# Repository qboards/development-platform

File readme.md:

# Modular Development Board

This board is essentially a breakout board for power, communication
and IO ports to a microcontroller or other suitable device. Multiple 
minimal microcontroller boards can be connected and easily swapped out
to have a full featured development board, that is not permanently tied
to a single microcontroller.

> TODO: list of modules

## Dev board Connector

> TODO

### Pinout

| Pin number | Function   |   | Pin number | Function  |   | Pin number | Function |   | Pin number | Function |
|------------|------------|---|------------|-----------|---|------------|----------|---|------------|----------|
|          1 | GND        |   |         21 | PORTA_6   |   |         41 | PORTB_8  |   |         61 | PORTD_2  |
|          2 | GND        |   |         22 | COMM_TX_2 |   |         42 | ICSP4    |   |         62 | PORTE_8  |
|          3 | VBUS       |   |         23 | PORTA_7   |   |         43 | PORTC_1  |   |         63 | PORTD_3  |
|          4 | VBUS       |   |         24 | COMM_RX_2 |   |         44 | ICSP5    |   |         64 | PORTE_7  |
|          5 | 5v         |   |         25 | PORTA_8   |   |         45 | PORTC_2  |   |         65 | PORTD_4  |
|          6 | 5v         |   |         26 | COMM_TX_3 |   |         46 | ICSP6    |   |         66 | PORTE_6  |
|          7 | 3v3        |   |         27 | PORTB_1   |   |         47 | PORTC_3  |   |         67 | PORTD_5  |
|          8 | 3v3        |   |         28 | COMM_RX_3 |   |         48 | ICSP7    |   |         68 | PORTE_5  |
|          9 | 1v8        |   |         29 | PORTB_2   |   |         49 | PORTC_4  |   |         69 | PORTD_6  |
|         10 | 1v8        |   |         30 | COMM_TX_4 |   |         50 | ICSP8    |   |         70 | PORTE_4  |
|         11 | PORTA_1    |   |         31 | PORTB_3   |   |         51 | PORTC_5  |   |         71 | PORTD_7  |
|         12 | COMM_RTS_1 |   |         32 | COMM_RX_4 |   |         52 | ICSP9    |   |         72 | PORTE_3  |
|         13 | PORTA_2    |   |         33 | PORTB_4   |   |         53 | PORTC_6  |   |         73 | PORTD_8  |
|         14 | COMM_CTS_1 |   |         34 | NC        |   |         54 | ICSP10   |   |         74 | PORTE_2  |
|         15 | PORTA_3    |   |         35 | PORTB_5   |   |         55 | PORTC_7  |   |         75 | NC       |
|         16 | COMM_DTR_1 |   |         36 | ICSP1     |   |         56 | NC       |   |         76 | PORTE_1  |
|         17 | PORTA_4    |   |         37 | PORTB_6   |   |         57 | PORTC_8  |   |         77 | VBUS     |
|         18 | COMM_TX_1  |   |         38 | ICSP2     |   |         58 | RST_A    |   |         78 | VBUS     |
|         19 | PORTA_5    |   |         39 | PORTB_7   |   |         59 | PORTD_1  |   |         79 | GND      |
|         20 | COMM_RX_1  |   |         40 | ICSP3     |   |         60 | RST_B    |   |         80 | GND      |

## Power supply

Input power can be delivered through the external power (barrel jack or 
screw terminals) or the USB connector. Selecting power from either the 
external inputs or the USB connector can be done with the **Power source** 
jumper.

Input on the external power terminals should be in the range
of 6 up to 15 volt. The polarity on the external input does not matter,
the development board will correct the polarity.

> TODO: Add current requirements.

The input power is regulated to 5V, 3.3V and 1.8V rails, which are 
all supplied to the development module. The module itself can pick one
of those rails and feed that rail back as VCC. For all rails and the 
ground rail test points are supplied.

> TODO: Add description of protection

## Communication

There are four serial ports that modules can expose, one fully featured (TX, RX, 
DTR, CTS, RTS) and three basic (TX, RX only). The development board has a single
USB to serial UART interface (FTDI FT232RL) connected to the USB input and the
other end can be connected with the jumper interfaces to any of the four serial
connections to the development module.

> TODO: Add image of communication jumpers

There are two LED indicators for TX and RX activity.

## Port modules

> TODO

## In Circuit Programming (ICP)

| ICP Pin | AVR Function |
|---------|--------------|
|       1 | MOSI         |
|       2 | VCC (VBUS)   |
|       3 | Unused (NC)  |
|       4 | GND          |
|       5 | RESET        |
|       6 | GND          |
|       7 | SCK          |
|       8 | GND          |
|       9 | MISO         |
|      10 | GND          |

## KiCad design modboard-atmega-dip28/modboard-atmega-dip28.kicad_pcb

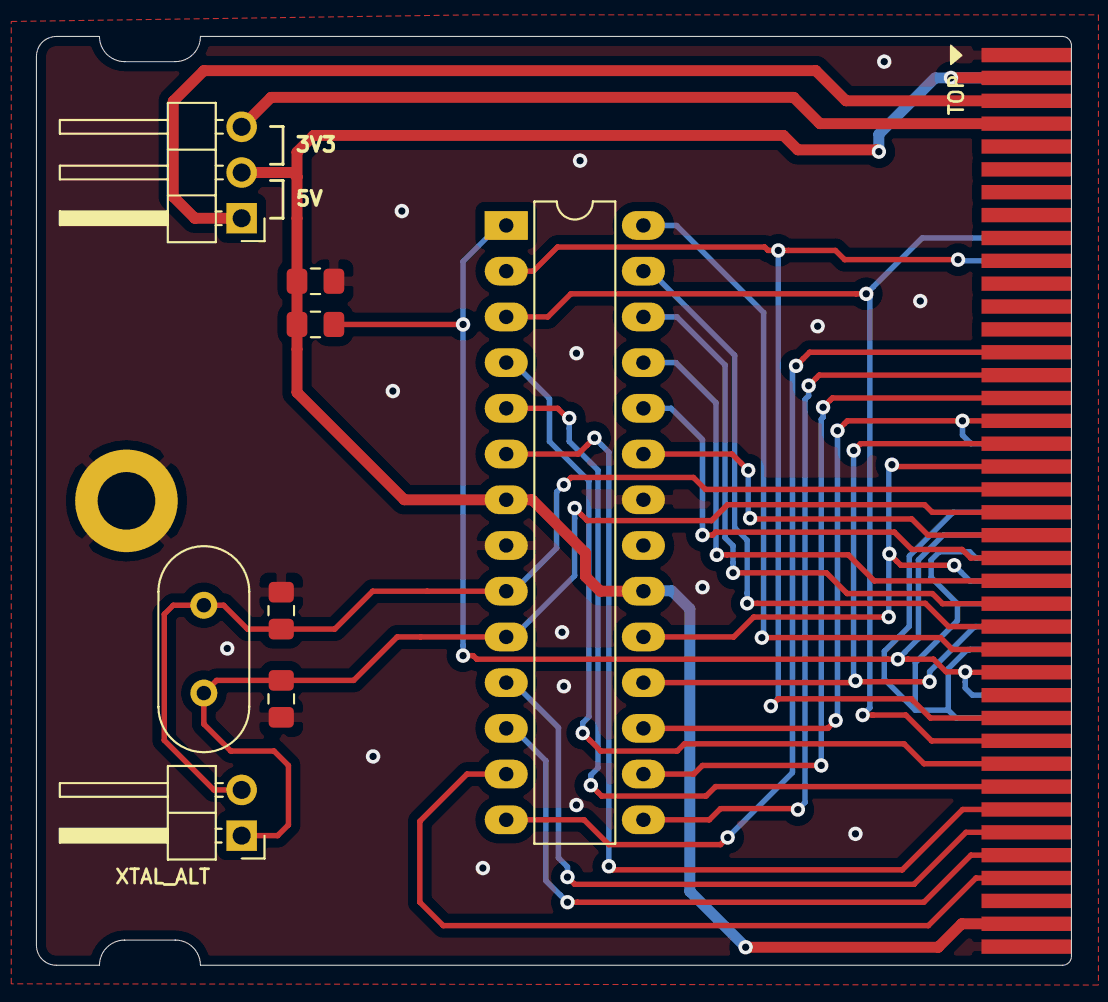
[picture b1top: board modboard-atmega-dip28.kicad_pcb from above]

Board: 2 copper layers, 57.5 x 51.6 mm, 11 parts (1 on the bottom side), 27 nets.

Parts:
ATmega-DIP28: LOGO_BRD_REF; logo_url-5mm
C1, C2, C3: C; C_0805_2012Metric_Pad1.15x1.40mm_HandSolder
H1: MountingHole_Pad; MountingHole_3.2mm_M3_ISO7380_Pad
J1: modboard-edge-connector; modboard_edge_connector
J2: Conn_01x03_Male; PinHeader_1x03_P2.54mm_Horizontal
R1: 10K; R_0805_2012Metric_Pad1.15x1.40mm_HandSolder
U1: ATMEGA328P-PU; DIP-28_W7.62mm_LongPads
XTAL_ALT: Conn_01x02_Male; PinHeader_1x02_P2.54mm_Horizontal
Y1: Crystal; Crystal_HC49-4H_Vertical

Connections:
GND: C1.2, C2.2, C3.2, H1.1, J1.1, J1.2, J1.42, J1.46, J1.50, J1.54, J1.60, J1.79, J1.80, U1.8, U1.22
MISO: J1.35, J1.52, U1.18
MOSI: J1.33, J1.36, U1.17
unnamed: C2.1, J1.39, U1.9, XTAL_ALT.2, Y1.1
unnamed: C3.1, J1.41, U1.10, XTAL_ALT.1, Y1.2
unnamed: J1.5, J1.6, J2.1
unnamed: J1.7, J1.8, J2.3
unnamed: J1.27, U1.14
unnamed: J1.29, U1.15
unnamed: J1.31, U1.16
unnamed: J1.43, U1.23
unnamed: J1.45, U1.24
unnamed: J1.47, U1.25
unnamed: J1.49, U1.26
unnamed: J1.51, U1.27
unnamed: J1.53, U1.28
unnamed: J1.63, U1.4
unnamed: J1.65, U1.5
unnamed: J1.67, U1.6
unnamed: J1.69, U1.11
unnamed: J1.71, U1.12
unnamed: J1.73, U1.13
RESET: J1.44, J1.55, J1.58, R1.2, U1.1
RX: J1.20, J1.59, U1.2
SCK: J1.37, J1.48, U1.19
TX: J1.18, J1.61, U1.3
VCC: C1.1, J1.3, J1.4, J1.77, J1.78, J2.2, R1.1, U1.7, U1.20

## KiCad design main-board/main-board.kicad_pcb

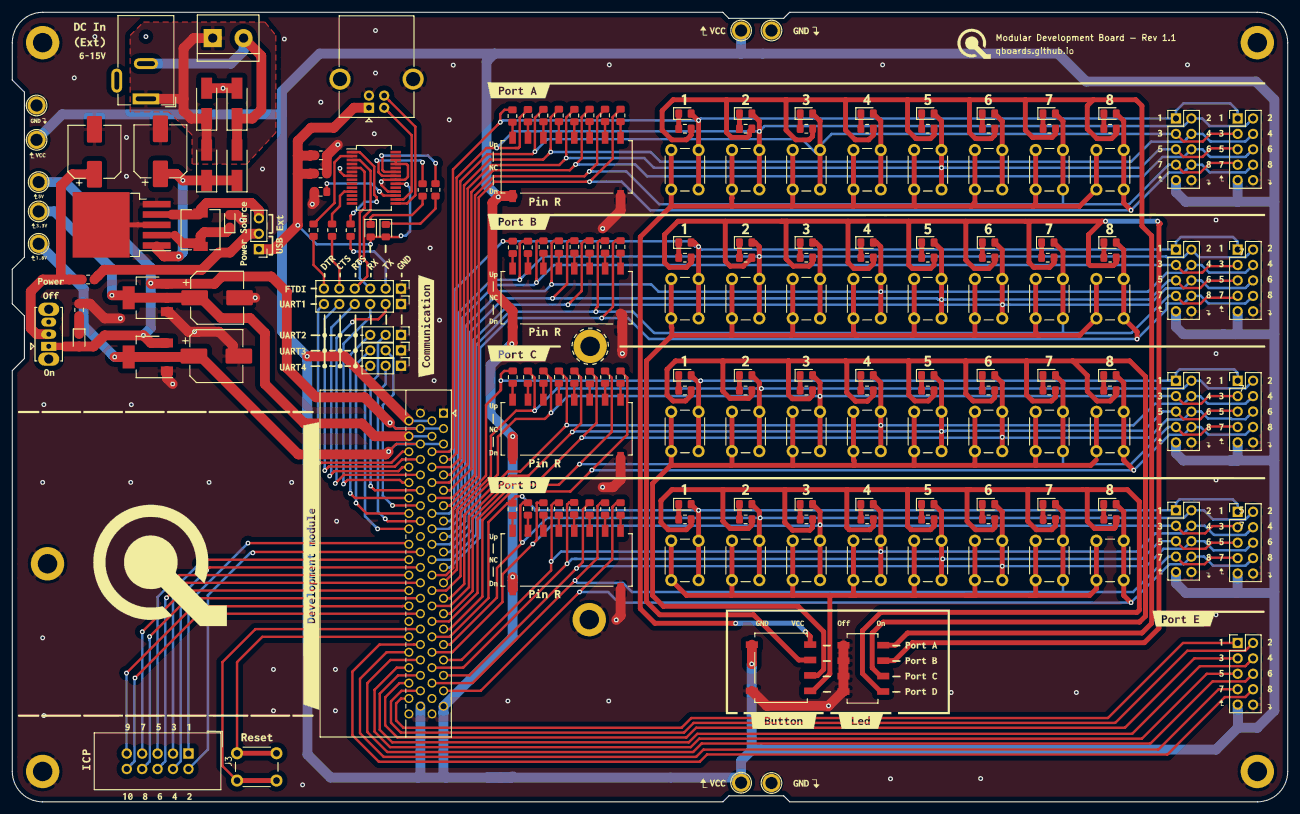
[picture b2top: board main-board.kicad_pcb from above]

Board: 2 copper layers, 210.0 x 130.0 mm, 201 parts (0 on the bottom side), 164 nets.

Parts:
C1: 100uF; CP_Elec_8x10.5
C2: 1000uF; CP_Elec_8x10.5
C3, C4: 22uF; CP_Elec_8x10.5
C5: 10uF; C_0805_2012Metric_Pad1.15x1.40mm_HandSolder
C6, C7: 100nF; C_0805_2012Metric_Pad1.15x1.40mm_HandSolder
D1, D2, D3, D4: 1N4007; D_SMA_Handsoldering
D5: D_Schottky_Small; D_SOD-323_HandSoldering
D6, D7, D8, D9, D10, D11, D12, D13, D14, D15, D16, D17, D18, D19, D20, D21, D22, D23, D24, D25, D26, D27, D28, D29, D30, D31, D32, D33, D34, D35, D36, D37: LED_Small; LED_0805_2012Metric_Pad1.15x1.40mm_HandSolder
D38: PWR_EN; LED_0805_2012Metric_Pad1.15x1.40mm_HandSolder
F1: 500mA; Fuse_0805_2012Metric_Pad1.15x1.40mm_HandSolder
H1, H2, H3, H4, H5, H6, H7: MountingHole_Pad; MountingHole_3.2mm_M3_ISO14580_Pad
J1: PWR_SELECT; PinHeader_1x03_P2.54mm_Vertical
J2: COMM1; PinHeader_1x06_P2.54mm_Vertical
J3: ICSP; IDC-Header_2x05_P2.54mm_Vertical
J5: COMM_2; PinHeader_1x03_P2.54mm_Vertical
J7, J8, J9, J10, J11, J12, J13, J14, J15: Conn_02x05_Odd_Even; PinHeader_2x05_P2.54mm_Vertical
J16: COMM_3; PinHeader_1x03_P2.54mm_Vertical
J17: Modular board connector; 4UCON_10156_2x40_P1.27mm_Socket_Horizontal
J18: PWR_EXT_1; BarrelJack_Wuerth_6941xx301002
J19: PWR_EXT_2; TerminalBlock_bornier-2_P5.08mm
J20: COMM_4; PinHeader_1x03_P2.54mm_Vertical
J21: COMM_OUT; PinHeader_1x06_P2.54mm_Vertical
L1: 100uH; L_6.3x6.3_H3
Modular Development Board - Rev 1.1: LOGO_BRD_REF; logo_url-5mm
R1, R42, R43, R44, R45, R46, R47, R48, R49, R50, R51, R52, R53, R54, R55, R56, R57, R58, R59, R60, R61, R62, R63, R64, R65, R66, R67, R68, R69, R70, R71, R72: 4K7; R_0805_2012Metric_Pad1.15x1.40mm_HandSolder
R2, R6, R7: 1K; R_0805_2012Metric_Pad1.15x1.40mm_HandSolder
R3, R4, R5: 10K; R_0805_2012Metric_Pad1.15x1.40mm_HandSolder
R10, R11, R12, R13, R14, R15, R16, R17, R18, R19, R20, R21, R22, R23, R24, R25, R26, R27, R28, R29, R30, R31, R32, R33, R34, R35, R36, R37, R38, R39, R40, R41: 10k; R_0805_2012Metric_Pad1.15x1.40mm_HandSolder
RX1: LED_Small; LED_0805_2012Metric_Pad1.15x1.40mm_HandSolder
SW1: RESET; SW_PUSH_6mm
SW2: BTN_LEVEL; TE_TDS04SG
SW3: LED_GND; TE_EDS04SG
SW4, SW5, SW6, SW7, SW8, SW9, SW10, SW11, SW13, SW14, SW15, SW16, SW17, SW18, SW19, SW20, SW22, SW23, SW24, SW25, SW26, SW27, SW28, SW29, SW31, SW32, SW33, SW34, SW35, SW36, SW37, SW38: SW_Push; SW_PUSH_6mm
SW12, SW21, SW30, SW39: SW_SP3T_x08; TE_TDS08SG
SW41: PWR_EN; SW_Slide_1P2T_CK_OS102011MS2Q
TP_1V1: 1V8; TestPoint_Plated_Hole_D2.0mm
TP_3V3: 3V3; TestPoint_Plated_Hole_D2.0mm
TP_5V1: 5V; TestPoint_Plated_Hole_D2.0mm
TP_GND1, TP_GND2, TP_GND3: GND; TestPoint_Plated_Hole_D2.0mm
TP_VBUS1, TP_VBUS2, TP_VBUS3: VBUS; TestPoint_Plated_Hole_D2.0mm
TX1: LED_Small; LED_0805_2012Metric_Pad1.15x1.40mm_HandSolder
U1: LM2576HVS-5; TO-263-5_TabPin3
U2: AP1117-33; SOT-223-3_TabPin2
U3: AP1117-18; SOT-223-3_TabPin2
U4: FT232RL; SSOP-28_5.3x10.2mm_P0.65mm
USB_1: USB_B; USB_B_OST_USB-B1HSxx_Horizontal
[BRD_REF]: LOGO_BRD_REF; logo-20mm

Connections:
+1V8: C4.1, J17.9, J17.10, TP_1V1.1, U3.2
+3V3: C3.1, J17.7, J17.8, TP_3V3.1, U2.2
+5V: D38.2, J17.5, J17.6, SW41.1, TP_5V1.1, U2.3, U3.3
/PORT_A_BTN_LEVEL: SW2.1, SW4.2, SW5.2, SW6.2, SW7.2, SW8.2, SW9.2, SW10.2, SW11.2
/PORT_A_LED_GND: R10.1, R11.1, R12.1, R13.1, R14.1, R15.1, R16.1, R17.1, SW3.2
/PORT_A_PIN1: D6.2, J7.1, J8.1, J17.11, R1.1, SW4.1
/PORT_A_PIN2: D7.2, J7.2, J8.2, J17.13, R42.1, SW5.1
/PORT_A_PIN3: D8.2, J7.3, J8.3, J17.15, R43.1, SW6.1
/PORT_A_PIN4: D9.2, J7.4, J8.4, J17.17, R44.1, SW7.1
/PORT_A_PIN5: D10.2, J7.5, J8.5, J17.19, R45.1, SW8.1
/PORT_A_PIN6: D11.2, J7.6, J8.6, J17.21, R46.1, SW9.1
/PORT_A_PIN7: D12.2, J7.7, J8.7, J17.23, R47.1, SW10.1
/PORT_A_PIN8: D13.2, J7.8, J8.8, J17.25, R48.1, SW11.1
/PORT_B_BTN_LEVEL: SW2.2, SW13.2, SW14.2, SW15.2, SW16.2, SW17.2, SW18.2, SW19.2, SW20.2
/PORT_B_LED_GND: R18.1, R19.1, R20.1, R21.1, R22.1, R23.1, R24.1, R25.1, SW3.4
/PORT_B_PIN1: D14.2, J9.1, J10.1, J17.27, R49.1, SW13.1
/PORT_B_PIN2: D15.2, J9.2, J10.2, J17.29, R50.1, SW14.1
/PORT_B_PIN3: D16.2, J9.3, J10.3, J17.31, R51.1, SW15.1
/PORT_B_PIN4: D17.2, J9.4, J10.4, J17.33, R52.1, SW16.1
/PORT_B_PIN5: D18.2, J9.5, J10.5, J17.35, R53.1, SW17.1
/PORT_B_PIN6: D19.2, J9.6, J10.6, J17.37, R54.1, SW18.1
/PORT_B_PIN7: D20.2, J9.7, J10.7, J17.39, R55.1, SW19.1
/PORT_B_PIN8: D21.2, J9.8, J10.8, J17.41, R56.1, SW20.1
/PORT_C_BTN_LEVEL: SW2.3, SW22.2, SW23.2, SW24.2, SW25.2, SW26.2, SW27.2, SW28.2, SW29.2
/PORT_C_LED_GND: R26.1, R27.1, R28.1, R29.1, R30.1, R31.1, R32.1, R33.1, SW3.6
/PORT_C_PIN1: D22.2, J11.1, J12.1, J17.43, R57.1, SW22.1
/PORT_C_PIN2: D23.2, J11.2, J12.2, J17.45, R58.1, SW23.1
/PORT_C_PIN3: D24.2, J11.3, J12.3, J17.47, R59.1, SW24.1
/PORT_C_PIN4: D25.2, J11.4, J12.4, J17.49, R60.1, SW25.1
/PORT_C_PIN5: D26.2, J11.5, J12.5, J17.51, R61.1, SW26.1
/PORT_C_PIN6: D27.2, J11.6, J12.6, J17.53, R62.1, SW27.1
/PORT_C_PIN7: D28.2, J11.7, J12.7, J17.55, R63.1, SW28.1
/PORT_C_PIN8: D29.2, J11.8, J12.8, J17.57, R64.1, SW29.1
/PORT_D_BTN_LEVEL: SW2.4, SW31.2, SW32.2, SW33.2, SW34.2, SW35.2, SW36.2, SW37.2, SW38.2
/PORT_D_LED_GND: R34.1, R35.1, R36.1, R37.1, R38.1, R39.1, R40.1, R41.1, SW3.8
/PORT_D_PIN1: D30.2, J13.1, J14.1, J17.59, R65.1, SW31.1
/PORT_D_PIN2: D31.2, J13.2, J14.2, J17.61, R66.1, SW32.1
/PORT_D_PIN3: D32.2, J13.3, J14.3, J17.63, R67.1, SW33.1
/PORT_D_PIN4: D33.2, J13.4, J14.4, J17.65, R68.1, SW34.1
/PORT_D_PIN5: D34.2, J13.5, J14.5, J17.67, R69.1, SW35.1
/PORT_D_PIN6: D35.2, J13.6, J14.6, J17.69, R70.1, SW36.1
/PORT_D_PIN7: D36.2, J13.7, J14.7, J17.71, R71.1, SW37.1
/PORT_D_PIN8: D37.2, J13.8, J14.8, J17.73, R72.1, SW38.1
/PORT_E_PIN1: J15.1, J17.76
/PORT_E_PIN2: J15.2, J17.74
/PORT_E_PIN3: J15.3, J17.72
/PORT_E_PIN4: J15.4, J17.70
/PORT_E_PIN5: J15.5, J17.68
/PORT_E_PIN6: J15.6, J17.66
/PORT_E_PIN7: J15.7, J17.64
/PORT_E_PIN8: J15.8, J17.62
GND: C1.2, C2.2, C3.2, C4.2, C5.1, C6.1, C7.2, D1.2, D3.2, D5.2, H1.1, H2.1, H3.1, H4.1, H5.1, H6.1, H7.1, J2.1, J5.1, J7.10, J8.10, J9.10, J10.10, J11.10, J12.10, J13.10, J14.10, J15.10, J16.1, J17.1, J17.2, J17.79, J17.80, J20.1, J21.1, R2.2, SW2.-, SW3.1, SW3.3, SW3.5, SW3.7, SW12.-, SW21.-, SW30.-, SW39.-, TP_GND1.1, TP_GND2.1, TP_VBUS2.1, U1.3, U1.5, U2.1, U3.1, U4.7, U4.18, U4.21, U4.25, U4.26, USB_1.4, USB_1.5
ICSP1: J3.1, J17.36
ICSP2: J3.2, J17.38
ICSP3: J3.3, J17.40
ICSP4: J3.4, J17.42
ICSP5: J3.5, J17.44
ICSP6: J3.6, J17.46
ICSP7: J3.7, J17.48
ICSP8: J3.8, J17.50
ICSP9: J3.9, J17.52
ICSP10: J3.10, J17.54
unnamed: C1.1, D2.1, D4.1, U1.1
unnamed: C2.1, F1.1, SW41.2
unnamed: C5.2, C6.2, J1.1, RX1.2, TX1.2, U4.20, USB_1.1
unnamed: C7.1, U4.17
unnamed: D1.1, D2.2, J18.1, J19.1
unnamed: D3.1, D4.2, J18.2, J19.2
unnamed: D5.1, L1.1, U1.2
unnamed: D6.1, R10.2
unnamed: D7.1, R11.2
unnamed: D8.1, R12.2
unnamed: D9.1, R13.2
unnamed: D10.1, R14.2
unnamed: D11.1, R15.2
unnamed: D12.1, R16.2
unnamed: D13.1, R17.2
unnamed: D14.1, R18.2
unnamed: D15.1, R19.2
unnamed: D16.1, R20.2
unnamed: D17.1, R21.2
unnamed: D18.1, R22.2
unnamed: D19.1, R23.2
unnamed: D20.1, R24.2
unnamed: D21.1, R25.2
unnamed: D22.1, R26.2
unnamed: D23.1, R27.2
unnamed: D24.1, R28.2
unnamed: D25.1, R29.2
unnamed: D26.1, R30.2
unnamed: D27.1, R31.2
unnamed: D28.1, R32.2
unnamed: D29.1, R33.2
unnamed: D30.1, R34.2
unnamed: D31.1, R35.2
unnamed: D32.1, R36.2
unnamed: D33.1, R37.2
unnamed: D34.1, R38.2
unnamed: D35.1, R39.2
unnamed: D36.1, R40.2
unnamed: D37.1, R41.2
unnamed: D38.1, R2.1
unnamed: F1.2, J1.2
unnamed: J1.3, L1.2, U1.4
unnamed: J16.2, J17.26
unnamed: J16.3, J17.28
unnamed: J2.6, J17.12
unnamed: J2.5, J17.14
unnamed: J2.4, J17.16
unnamed: J2.2, J17.18
unnamed: J2.3, J17.20
unnamed: J5.2, J17.22
unnamed: J5.3, J17.24
unnamed: J17.30, J20.2
unnamed: J17.32, J20.3
unnamed: J17.58, SW1.2
unnamed: J17.60, SW1.1
unnamed: J21.2, R3.2
unnamed: J21.3, U4.5
unnamed: J21.4, U4.3
unnamed: J21.5, R4.2
unnamed: J21.6, R5.2
unnamed: R1.2, SW12.1
unnamed: R3.1, U4.1
unnamed: R4.1, U4.11
unnamed: R5.1, U4.2
unnamed: R6.1, TX1.1
unnamed: R6.2, U4.23
unnamed: R7.1, U4.22
unnamed: R7.2, RX1.1
unnamed: R42.2, SW12.2
unnamed: R43.2, SW12.3
unnamed: R44.2, SW12.4
unnamed: R45.2, SW12.5
unnamed: R46.2, SW12.6
unnamed: R47.2, SW12.7
unnamed: R48.2, SW12.8
unnamed: R49.2, SW21.1
unnamed: R50.2, SW21.2
unnamed: R51.2, SW21.3
unnamed: R52.2, SW21.4
unnamed: R53.2, SW21.5
unnamed: R54.2, SW21.6
unnamed: R55.2, SW21.7
unnamed: R56.2, SW21.8
unnamed: R57.2, SW30.1
unnamed: R58.2, SW30.2
unnamed: R59.2, SW30.3
unnamed: R60.2, SW30.4
unnamed: R61.2, SW30.5
unnamed: R62.2, SW30.6
unnamed: R63.2, SW30.7
unnamed: R64.2, SW30.8
unnamed: R65.2, SW39.1
unnamed: R66.2, SW39.2
unnamed: R67.2, SW39.3
unnamed: R68.2, SW39.4
unnamed: R69.2, SW39.5
unnamed: R70.2, SW39.6
unnamed: R71.2, SW39.7
unnamed: R72.2, SW39.8
unnamed: U4.15, USB_1.3
unnamed: U4.16, USB_1.2
VBUS: J7.9, J8.9, J9.9, J10.9, J11.9, J12.9, J13.9, J14.9, J15.9, J17.3, J17.4, J17.77, J17.78, SW2.+, SW12.+, SW21.+, SW30.+, SW39.+, TP_GND3.1, TP_VBUS1.1, TP_VBUS3.1

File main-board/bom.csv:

Ref,Qnty,Value,Manufacturer,Manufacturer part nr,Package,Part,Farnell #
C1,1,100uF,MULTICOMP PRO,MCVKZ010M101FB3L,6.3x5.7,Polarized SMD capacitor,2611328
C2,1,1000uF,MULTICOMP PRO,MCVVT6R3M102FB3L,8x5.7,Polarized SMD capacitor,2611416
"C3, C4",2,22uF,MULTICOMP PRO,MCVVT063M220FB3L,6.3x5.7,Polarized SMD capacitor,2611407
C5,1,10uF,,,0805,Unpolarized SMD capacitor,
"C6, C7",2,100nF,,,0805,Unpolarized SMD capacitor,
"D1, D2, D3, D4",4,1N4007,,,SMA,"Diode, small symbol",
D5,1,,DIODES INC.,ZLLS400TA,0805,Small Signal Schottky Diode,3127494
"D6, D7, D8, D9, D10, D11, D12, D13, D14, D15, D16, D17, D18, D19, D20, D21, D22, D23, D24, D25, D26, D27, D28, D29, D30, D31, D32, D33, D34, D35, D36, D37, RX1, TX1",34,,KINGBRIGHT,KP-2012LSGC,0805,Low power SMD LED,2463991
D38,1,,KINGBRIGHT,KP-2012LSGC,0805,Low power SMD LED,2463991
F1,1,500mA,BOURNS,MF-PSMF050X-2,0805,"Resettable fuse, polymeric positive temperature coefficient",1294876
J1,1,,,,,"Pin header, 2.54mm, 1 row, 3 contacts",
J2,1,,,,,"Pin header, 2.54mm, 1 row, 6 contacts",
J3,1,,,,,"Pin header, 2.54mm, 2 rows, 10 contacts",
J4,1,,,,,"Pin header, 2.54mm, 2 rows, 6 contacts",
J5,1,,,,,"Pin header, 2.54mm, 1 row, 3 contacts",
"J7, J8, J9, J10, J11, J12, J13, J14, J15",9,,,,,"Pin header, 2.54mm, 2 rows, 10 contacts",
J16,1,,,,,"Pin header, 2.54mm, 1 row, 3 contacts",
J17,1,,KITRONIK,5601B,,Edge Connector (BBC micro:bit compatible),2563845
J18,1,,CLIFF ELECTRONIC COMPONENTS,FC68148,,"DC Barrel Jack Power Connector, 2.1mm",224959
J19,1,,,,,"Screw terminal, 1 row, 2 contacts",
J20,1,,,,,"Pin header, 2.54mm, 1 row, 3 contacts",
J21,1,,,,,"Pin header, 2.54mm, 1 row, 6 contacts",
L1,1,100uH,WURTH ELEKTRONIK,74404086101,,Power Inductor (SMD),2842174
"R2, R6, R7",3,1K,,,0805,SMD resistor,
"R3, R4, R5",3,10K,,,0805,SMD resistor,
"R8, R9",2,,,,0805,SMD resistor,
"R10, R11, R12, R13, R14, R15, R16, R17, R18, R19, R20, R21, R22, R23, R24, R25, R26, R27, R28, R29, R30, R31, R32, R33, R34, R35, R36, R37, R38, R39, R40, R41",32,10k,,,0805,SMD resistor,
SW1,1,,SCHURTER,1301.9303,,"Through hole tactile switch, 6mm",1217774
SW2,1,,ALCOSWITCH - TE CONNECTIVITY,TDS04SGNNTU04,,"DIP / SIP Switch, Raised Type, 4 Circuits, SP3T",2792778
SW3,1,,ALCOSWITCH - TE CONNECTIVITY,EDS04SGNNTU04Q,,"DIP / SIP Switch, Raised Type, 4 Circuits, SPST",2792676
"SW4, SW5, SW6, SW7, SW8, SW9, SW10, SW11, SW13, SW14, SW15, SW16, SW17, SW18, SW19, SW20, SW22, SW23, SW24, SW25, SW26, SW27, SW28, SW29, SW31, SW32, SW33, SW34, SW35, SW36, SW37, SW38",32,,SCHURTER,1301.9303,,"Through hole tactile switch, 6mm",1217774
"SW12, SW21, SW30, SW39",4,,ALCOSWITCH - TE CONNECTIVITY,TDS08SGNNTU04,,"DIP / SIP Switch, Raised Type, 8 Circuits, SP3T",2792779
SW41,1,,C & K COMPONENTS,OS102011MA1QN1,,"Slide Switch, SPDT, On-On, Through Hole",1201431
U1,1,,TEXAS INSTRUMENTS,LM2576HVS-5.0/NOPB,TO-263-5,"Buck (Step Down) Switching Regulator, Fixed, 4V-60V In, 5V And 3A Out, 52 kHz",2382943
U2,1,AP1117-33,DIODES INC.,AP1117E33G-13,SOT-223-3,"1A Low Dropout regulator, positive, 3.3V fixed output, SOT-223",1825291
U3,1,AP1117-18,DIODES INC.,AP1117E18G-13,SOT-223-3,"1A Low Dropout regulator, positive, 1.8V fixed output, SOT-223",1825289
U4,1,FT232RL,FTDI,FT232RL,SSOP-28,"USB to Serial Interface, SSOP-28",1146032
USB_1,1,,,,,USB Type B connector,

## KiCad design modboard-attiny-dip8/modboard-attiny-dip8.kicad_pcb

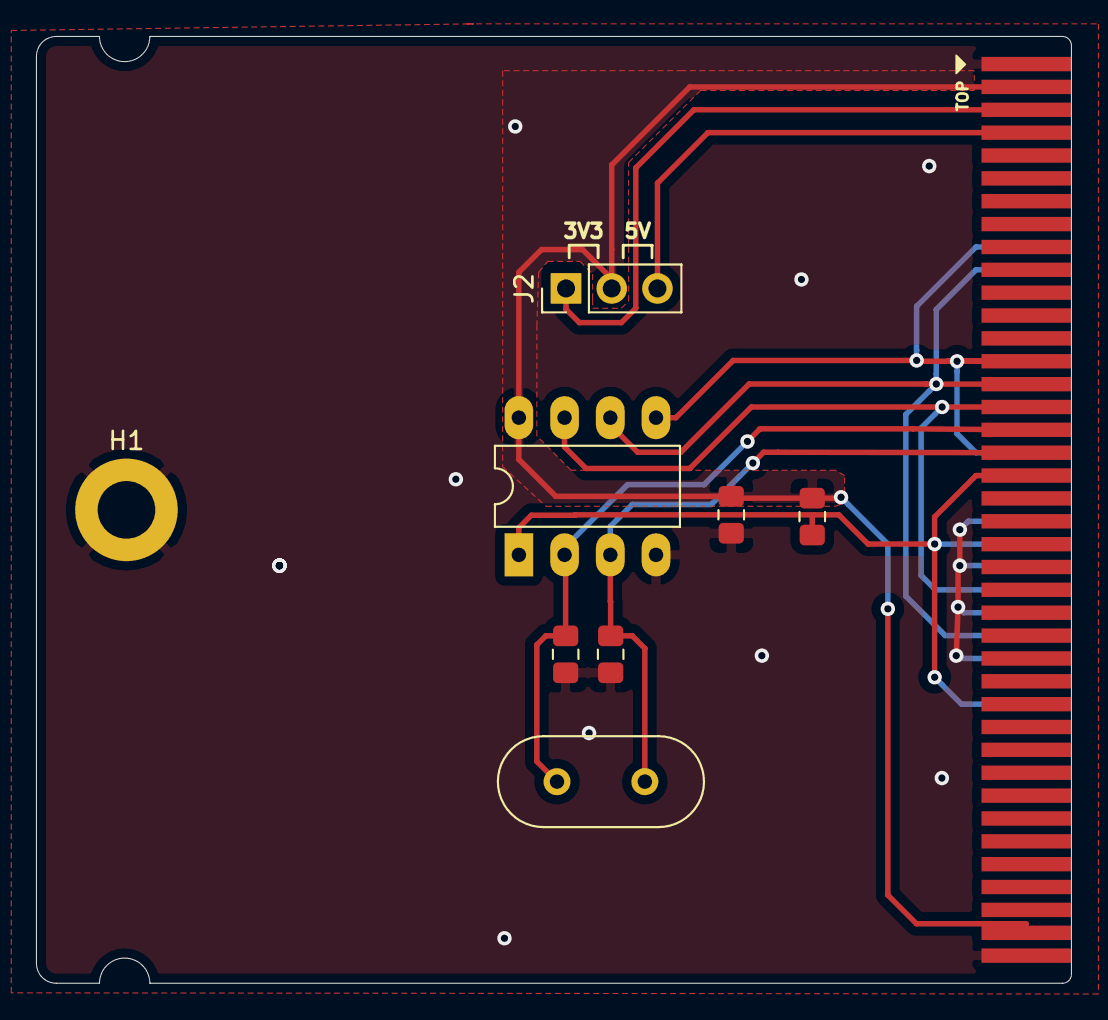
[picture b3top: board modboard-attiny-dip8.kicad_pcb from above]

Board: 2 copper layers, 57.5 x 52.6 mm, 10 parts (1 on the bottom side), 10 nets.

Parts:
ATTINY-DIP8: LOGO_BRD_REF; logo_url-5mm
C1, C2, C3: C; C_0805_2012Metric_Pad1.15x1.40mm_HandSolder
H1: MountingHole_Pad; MountingHole_3.2mm_M3_ISO7380_Pad
J1: modboard-edge-connector; modboard_edge_connector
J2: Conn_01x03_Male; PinHeader_1x03_P2.54mm_Vertical
R1: 10K; R_0805_2012Metric_Pad1.15x1.40mm_HandSolder
U1: ATTINY85-20PU; DIP-8_W7.62mm_LongPads
Y1: Crystal; Crystal_HC49-4H_Vertical

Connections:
GND: C1.2, C2.2, C3.2, H1.1, J1.1, J1.2, J1.42, J1.46, J1.50, J1.54, J1.60, J1.79, J1.80, U1.4
MISO: J1.20, J1.29, J1.52, U1.6
MOSI: J1.18, J1.27, J1.36, U1.5
unnamed: C2.1, J1.35, U1.3, Y1.1
unnamed: C3.1, J1.33, U1.2, Y1.2
unnamed: J1.5, J1.6, J2.1
unnamed: J1.7, J1.8, J2.3
RESET: J1.37, J1.44, J1.58, R1.2, U1.1
SCK: J1.31, J1.48, U1.7
VCC: C1.1, J1.3, J1.4, J1.77, J1.78, J2.2, R1.1, U1.8

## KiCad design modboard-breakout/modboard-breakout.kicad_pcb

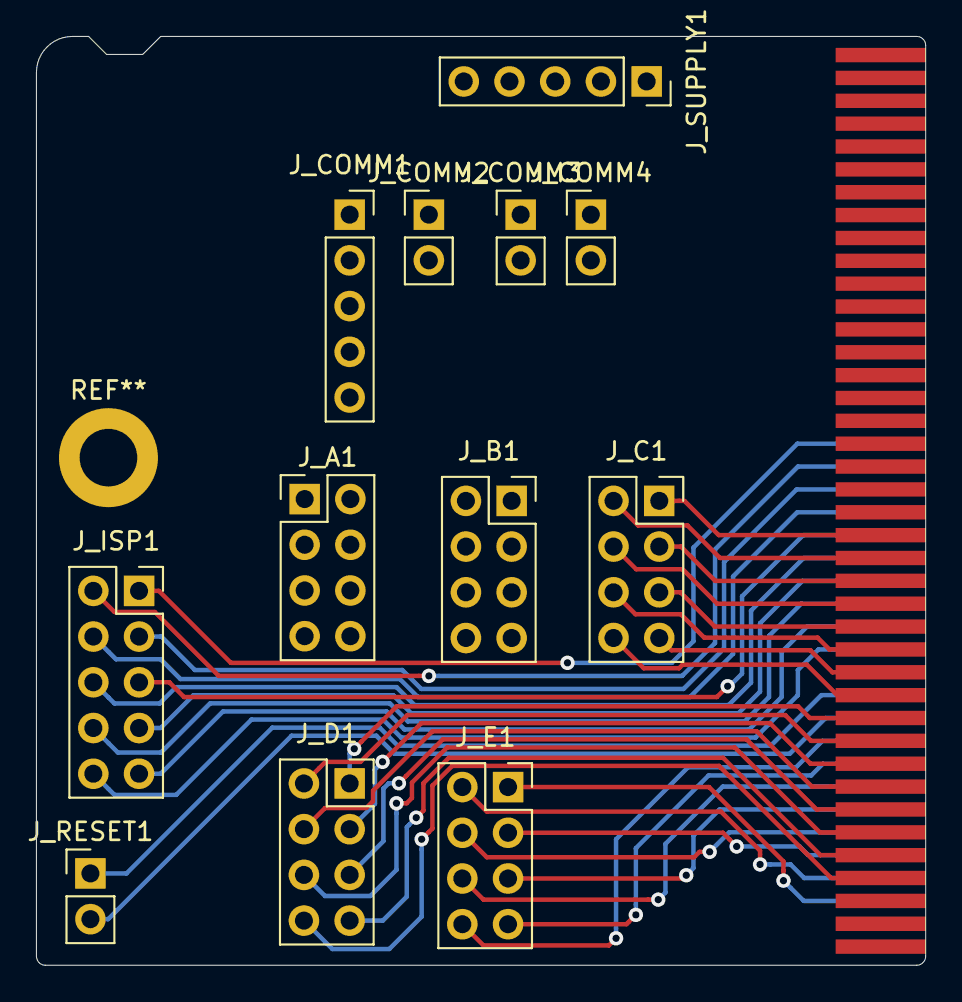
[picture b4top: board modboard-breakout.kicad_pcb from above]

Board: 2 copper layers, 49.4 x 51.6 mm, 13 parts (0 on the bottom side), 68 nets.

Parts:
J1: modboard-edge-connector; modboard_edge_connector
J_A1: Conn_02x04_Counter_Clockwise; PinHeader_2x04_P2.54mm_Vertical
J_B1: Conn_02x04_Counter_Clockwise; PinSocket_2x04_P2.54mm_Vertical
J_C1: Conn_02x04_Counter_Clockwise; PinSocket_2x04_P2.54mm_Vertical
J_COMM1: Conn_01x05; PinSocket_1x05_P2.54mm_Vertical
J_COMM2, J_COMM3, J_COMM4: Conn_01x02; PinHeader_1x02_P2.54mm_Vertical
J_D1: Conn_02x04_Counter_Clockwise; PinSocket_2x04_P2.54mm_Vertical
J_E1: Conn_02x04_Counter_Clockwise; PinSocket_2x04_P2.54mm_Vertical
J_ISP1: Conn_02x05_Counter_Clockwise; PinSocket_2x05_P2.54mm_Vertical
J_RESET1: Conn_01x02; PinHeader_1x02_P2.54mm_Vertical
J_SUPPLY1: Conn_01x05; PinSocket_1x05_P2.54mm_Vertical

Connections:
GND: J1.1, J1.2, J1.79, J1.80, J_SUPPLY1.5
unnamed: J1.3, J1.4, J1.77, J1.78, J_SUPPLY1.1
unnamed: J1.5, J1.6, J_SUPPLY1.2
unnamed: J1.7, J1.8, J_SUPPLY1.3
unnamed: J1.9, J1.10, J_SUPPLY1.4
unnamed: J1.11, J_A1.1
unnamed: J1.12, J_COMM1.5
unnamed: J1.13, J_A1.2
unnamed: J1.14, J_COMM1.4
unnamed: J1.15, J_A1.3
unnamed: J1.16, J_COMM1.3
unnamed: J1.17, J_A1.4
unnamed: J1.18, J_COMM1.1
unnamed: J1.19, J_A1.5
unnamed: J1.20, J_COMM1.2
unnamed: J1.21, J_A1.6
unnamed: J1.22, J_COMM2.1
unnamed: J1.23, J_A1.7
unnamed: J1.24, J_COMM2.2
unnamed: J1.25, J_A1.8
unnamed: J1.26, J_COMM3.1
unnamed: J1.27, J_B1.1
unnamed: J1.28, J_COMM3.2
unnamed: J1.29, J_B1.2
unnamed: J1.30, J_COMM4.1
unnamed: J1.31, J_B1.3
unnamed: J1.32, J_COMM4.2
unnamed: J1.33, J_B1.4
unnamed: J1.35, J_B1.5
unnamed: J1.36, J_ISP1.1
unnamed: J1.37, J_B1.6
unnamed: J1.38, J_ISP1.2
unnamed: J1.39, J_B1.7
unnamed: J1.40, J_ISP1.3
unnamed: J1.41, J_B1.8
unnamed: J1.42, J_ISP1.4
unnamed: J1.43, J_C1.1
unnamed: J1.44, J_ISP1.5
unnamed: J1.45, J_C1.2
unnamed: J1.46, J_ISP1.6
unnamed: J1.47, J_C1.3
unnamed: J1.48, J_ISP1.7
unnamed: J1.49, J_C1.4
unnamed: J1.50, J_ISP1.8
unnamed: J1.51, J_C1.5
unnamed: J1.52, J_ISP1.9
unnamed: J1.53, J_C1.6
unnamed: J1.54, J_ISP1.10
unnamed: J1.55, J_C1.7
unnamed: J1.57, J_C1.8
unnamed: J1.58, J_RESET1.1
unnamed: J1.59, J_D1.1
unnamed: J1.60, J_RESET1.2
unnamed: J1.61, J_D1.2
unnamed: J1.62, J_E1.8
unnamed: J1.63, J_D1.3
unnamed: J1.64, J_E1.7
unnamed: J1.65, J_D1.4
unnamed: J1.66, J_E1.6
unnamed: J1.67, J_D1.5
unnamed: J1.68, J_E1.5
unnamed: J1.69, J_D1.6
unnamed: J1.70, J_E1.4
unnamed: J1.71, J_D1.7
unnamed: J1.72, J_E1.3
unnamed: J1.73, J_D1.8
unnamed: J1.74, J_E1.2
unnamed: J1.76, J_E1.1

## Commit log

2020-05-08 Added inital readme with power supply requirements and thoughts
2020-05-17 Initial iteration
2020-06-27 First layout
2020-06-27 Changed button pullup-down selector
2020-06-27 Rotated isp connector
2020-06-27 Added filled zones
2020-06-27 Added module board hole
2020-10-18 Updated footprints
2020-10-21 Initial breakout board
2020-11-29 Updated silkscreens
2020-11-30 Cleaned up Dwgs.User
2020-11-30 Added QBoard logos
2020-11-30 Removed gitignore cache file
2020-11-30 Added sheet metadata
2020-11-30 Added pinout description
2020-11-30 Added communication description in readme
2020-12-07 Added bom
2020-12-07 Initial ATTiny DIP8 board
2020-12-27 Updated connector and board size
2020-12-27 Added ICP table in readme
2020-12-27 Added ICP connections, labeled VBUS header
2020-12-27 Added mounting hole, fixed routing
2021-01-01 Added logo
2021-01-01 Fixed GND plane
2021-01-01 Added rev number, added sheet data
2021-01-01 Fixed revision number
2021-01-11 Updated board size, connector and reference text
2021-01-12 Fixed top test point mislabeling
2021-01-12 Updated/fixed Qboards references
2021-01-21 Clarified R4,5,6 value, tidied F.SilkS and F,Fab
2021-01-23 Added pin pullups/downs instead of button level
2021-01-23 Fixed some routing
2021-01-23 Added pinout reference
2021-01-23 Added silkscreen image source
2021-01-23 Added probe cutouts
2021-01-23 Changed ICP header to IDC connector
2021-01-24 Added silkscreen
2021-01-25 Added final tweaks and logos
2021-02-03 Fixed DRC errors
2021-06-23 Routed edge connectors 44 (RESET) and 37 (PORTB_6)
